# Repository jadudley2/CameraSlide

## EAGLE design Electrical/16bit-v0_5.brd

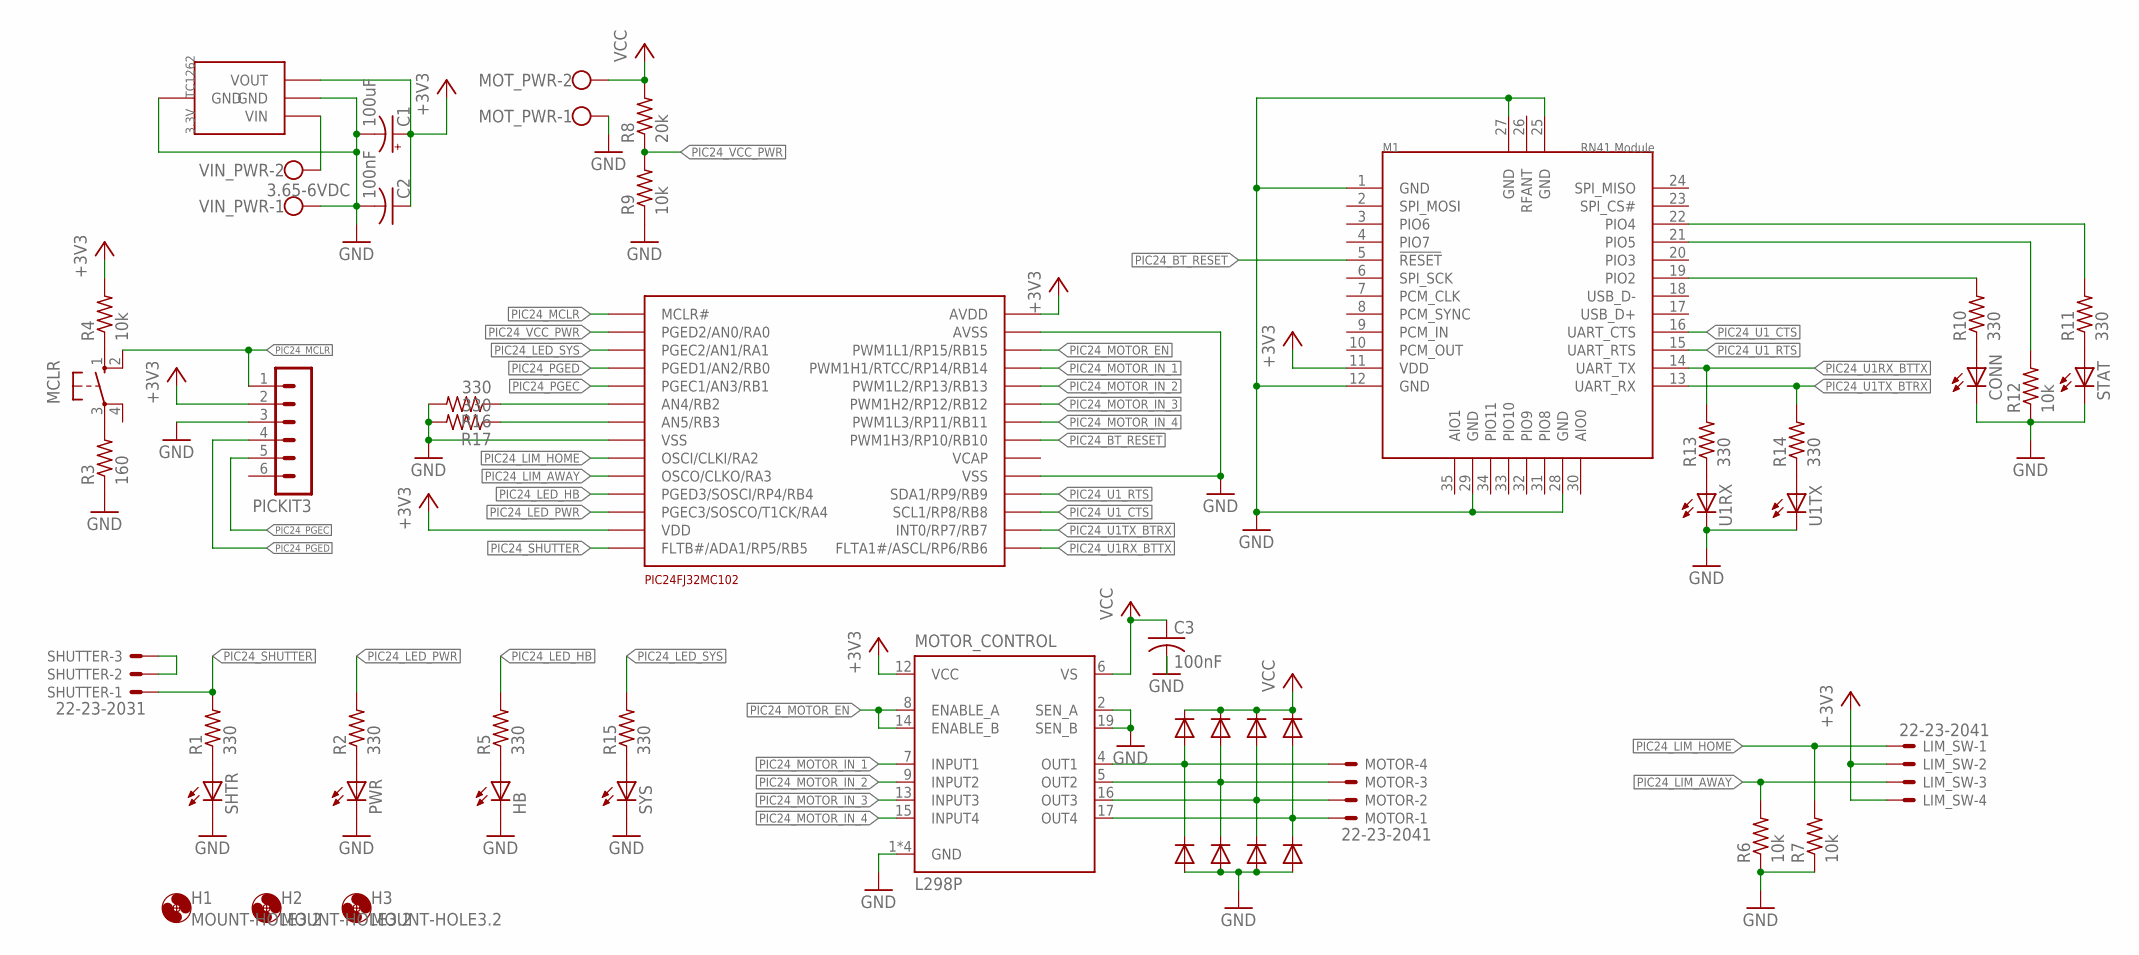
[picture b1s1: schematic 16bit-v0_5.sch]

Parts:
C1: 100uF; E2,5-7
C2, C3: 100nF; C0402
CONN: LED_ESML0603; LED_SML0603
D1, D2, D3, D4, D5, D6, D7, D8: DIODE-SMB; SMB
H1, H2, H3: MOUNT-HOLE3.2; 3,2
HB: LED_ESML0603; LED_SML0603
LIM_SW: 22-23-2041
MCLR: 10-XX; B3F-10XX
MOTOR: 22-23-2041
MOTOR_CONTROL: L298P; POWERSO-20
MOT_PWR: W237-102
PICKIT3: MA06-1
PWR: LED_ESML0603; LED_SML0603
R1, R2, R5, R10, R11, R13, R14, R15, R16, R17: 330; R0603
R3: 160; R0603
R4, R6, R7, R9, R12: 10k; R0603
R8: 20k; R0603
SHTR: LED_ESML0603; LED_SML0603
SHUTTER: 22-23-2031
STAT: LED_ESML0603; LED_SML0603
SYS: LED_ESML0603; LED_SML0603
U1RX, U1TX: LED_ESML0603; LED_SML0603
U$1: PIC24FJ32MC102; PIC2428-SOIC
U$2: RN41N
U$3: TC1262-3.3VDBTR; TO-261-4
VIN_PWR: 3.65-6VDC; W237-102

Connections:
+3V3: C1.+, C2.1, LIM_SW.2, LIM_SW.4, MOTOR_CONTROL.12 (VCC), PICKIT3.2, R4.2, U$1.AVDD, U$1.VDD, U$2.11 (VDD), U$3.P$3 (VOUT)
GND: C1.-, C2.2, C3.2, CONN.C, D5.A, D6.A, D7.A, D8.A, HB.C, MOTOR_CONTROL.1 (GND), MOTOR_CONTROL.2 (SEN_A), MOTOR_CONTROL.10 (GND), MOTOR_CONTROL.11 (GND), MOTOR_CONTROL.19 (SEN_B), MOTOR_CONTROL.20 (GND), MOT_PWR.1, PICKIT3.3, PWR.C, R3.1, R6.1, R7.1, R9.1, R12.1, R16.2, R17.2, SHTR.C, STAT.C, SYS.C, U1RX.C, U1TX.C, U$1.AVSS, U$1.VSS@8 (VSS), U$1.VSS@19 (VSS), U$2.1 (GND), U$2.12 (GND), U$2.25 (GND), U$2.27 (GND), U$2.28 (GND), U$2.29 (GND), U$3.P$2 (GND), U$3.P$4 (GND), VIN_PWR.1
MOTOR_OUT_1: D1.A, D5.C, MOTOR.4, MOTOR_CONTROL.4 (OUT1)
MOTOR_OUT_2: D2.A, D6.C, MOTOR.3, MOTOR_CONTROL.5 (OUT2)
MOTOR_OUT_3: D3.A, D7.C, MOTOR.2, MOTOR_CONTROL.16 (OUT3)
MOTOR_OUT_4: D4.A, D8.C, MOTOR.1, MOTOR_CONTROL.17 (OUT4)
unnamed: R13.1, U1RX.A
unnamed: MCLR.3, R3.2
unnamed: MCLR.1 (S), R4.1
unnamed: R1.1, SHTR.A
unnamed: R12.2, U$2.21 (PIO5)
unnamed: PWR.A, R2.1
unnamed: HB.A, R5.1
unnamed: R15.1, SYS.A
unnamed: R14.1, U1TX.A
unnamed: R11.2, U$2.22 (PIO4)
unnamed: R10.2, U$2.19 (PIO2)
unnamed: CONN.A, R10.1
unnamed: R11.1, STAT.A
PIC24_BT_!RESET: U$1.RB10 (PWM1H3/RP10/RB10), U$2.5 (!RESET)
PIC24_EXTRA_1: R16.1, U$1.RB2 (AN4/RB2)
PIC24_EXTRA_2: R17.1, U$1.RB3 (AN5/RB3)
PIC24_LED_HB: R5.2, U$1.RB4 (PGED3/SOSCI/RP4/RB4)
PIC24_LED_PWR: R2.2, U$1.RA4 (PGEC3/SOSCO/T1CK/RA4)
PIC24_LED_SYS: R15.2, U$1.RA1 (PGEC2/AN1/RA1)
PIC24_LIM_AWAY: LIM_SW.3, R6.2, U$1.RA3 (OSCO/CLKO/RA3)
PIC24_LIM_HOME: LIM_SW.1, R7.2, U$1.RA2 (OSCI/CLKI/RA2)
PIC24_MCLR: MCLR.2 (S1), PICKIT3.1, U$1.MCLR#
PIC24_MOTOR_EN: MOTOR_CONTROL.8 (ENABLE_A), MOTOR_CONTROL.14 (ENABLE_B), U$1.RB15 (PWM1L1/RP15/RB15)
PIC24_MOTOR_IN_1: MOTOR_CONTROL.7 (INPUT1), U$1.RB14 (PWM1H1/RTCC/RP14/RB14)
PIC24_MOTOR_IN_2: MOTOR_CONTROL.9 (INPUT2), U$1.RB13 (PWM1L2/RP13/RB13)
PIC24_MOTOR_IN_3: MOTOR_CONTROL.13 (INPUT3), U$1.RB12 (PWM1H2/RP12/RB12)
PIC24_MOTOR_IN_4: MOTOR_CONTROL.15 (INPUT4), U$1.RB11 (PWM1L3/RP11/RB11)
PIC24_PGEC: PICKIT3.5, U$1.PGEC1 (PGEC1/AN3/RB1)
PIC24_PGED: PICKIT3.4, U$1.PGED1 (PGED1/AN2/RB0)
PIC24_SHUTTER: R1.2, SHUTTER.1, U$1.RB5 (FLTB#/ADA1/RP5/RB5)
PIC24_U1RX_BTTX: R13.2, U$1.RB6 (FLTA1#/ASCL/RP6/RB6), U$2.14 (UART_TX)
PIC24_U1TX_BTRX: R14.2, U$1.RB7 (INT0/RP7/RB7), U$2.13 (UART_RX)
PIC24_U1_CTS: U$1.RB8 (SCL1/RP8/RB8), U$2.16 (UART_CTS)
PIC24_U1_RTS: U$1.RB9 (SDA1/RP9/RB9), U$2.15 (UART_RTS)
PIC24_VCC_PWR: R8.1, R9.2, U$1.RA0 (PGED2/AN0/RA0)
SHUTTER_SHORT: SHUTTER.2, SHUTTER.3
VCC: C3.1, D1.C, D2.C, D3.C, D4.C, MOTOR_CONTROL.6 (VS), MOT_PWR.2, R8.2
VIN_PWR: U$3.P$1 (VIN), VIN_PWR.2

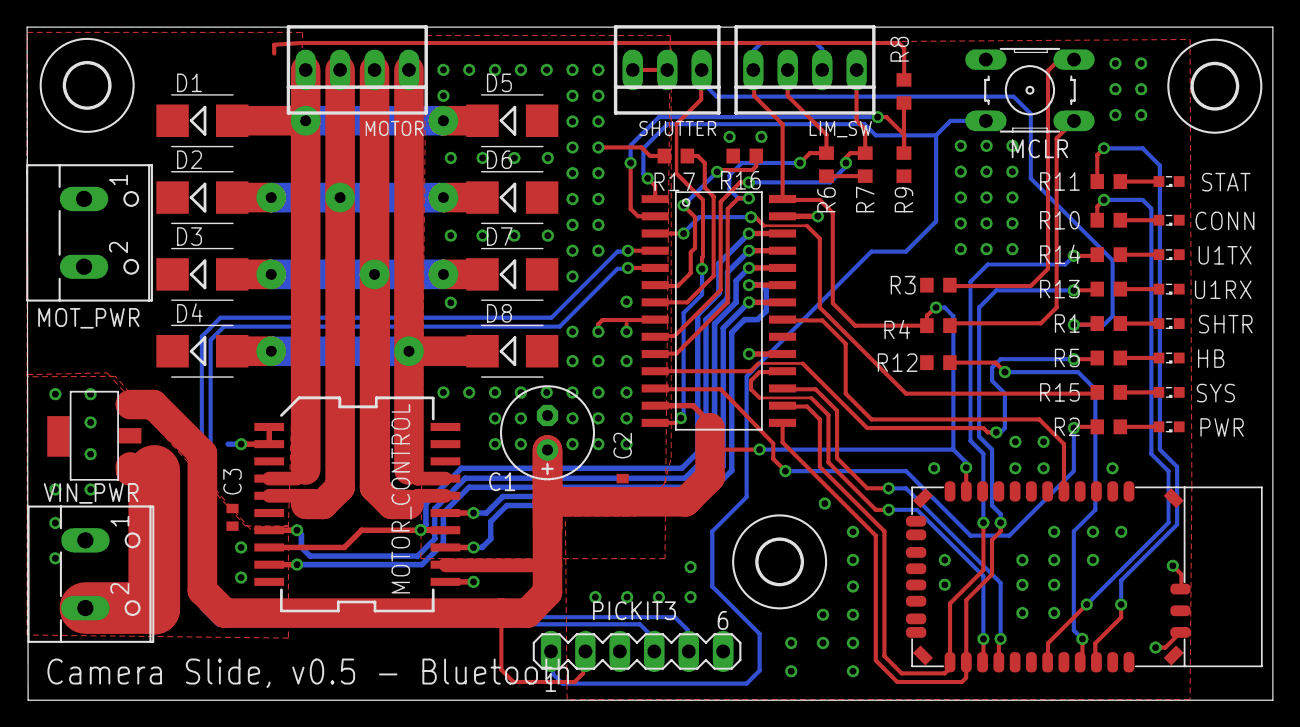
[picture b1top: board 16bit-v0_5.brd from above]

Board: 2 copper layers, 91.9 x 49.7 mm, 50 parts (0 on the bottom side), 44 nets.

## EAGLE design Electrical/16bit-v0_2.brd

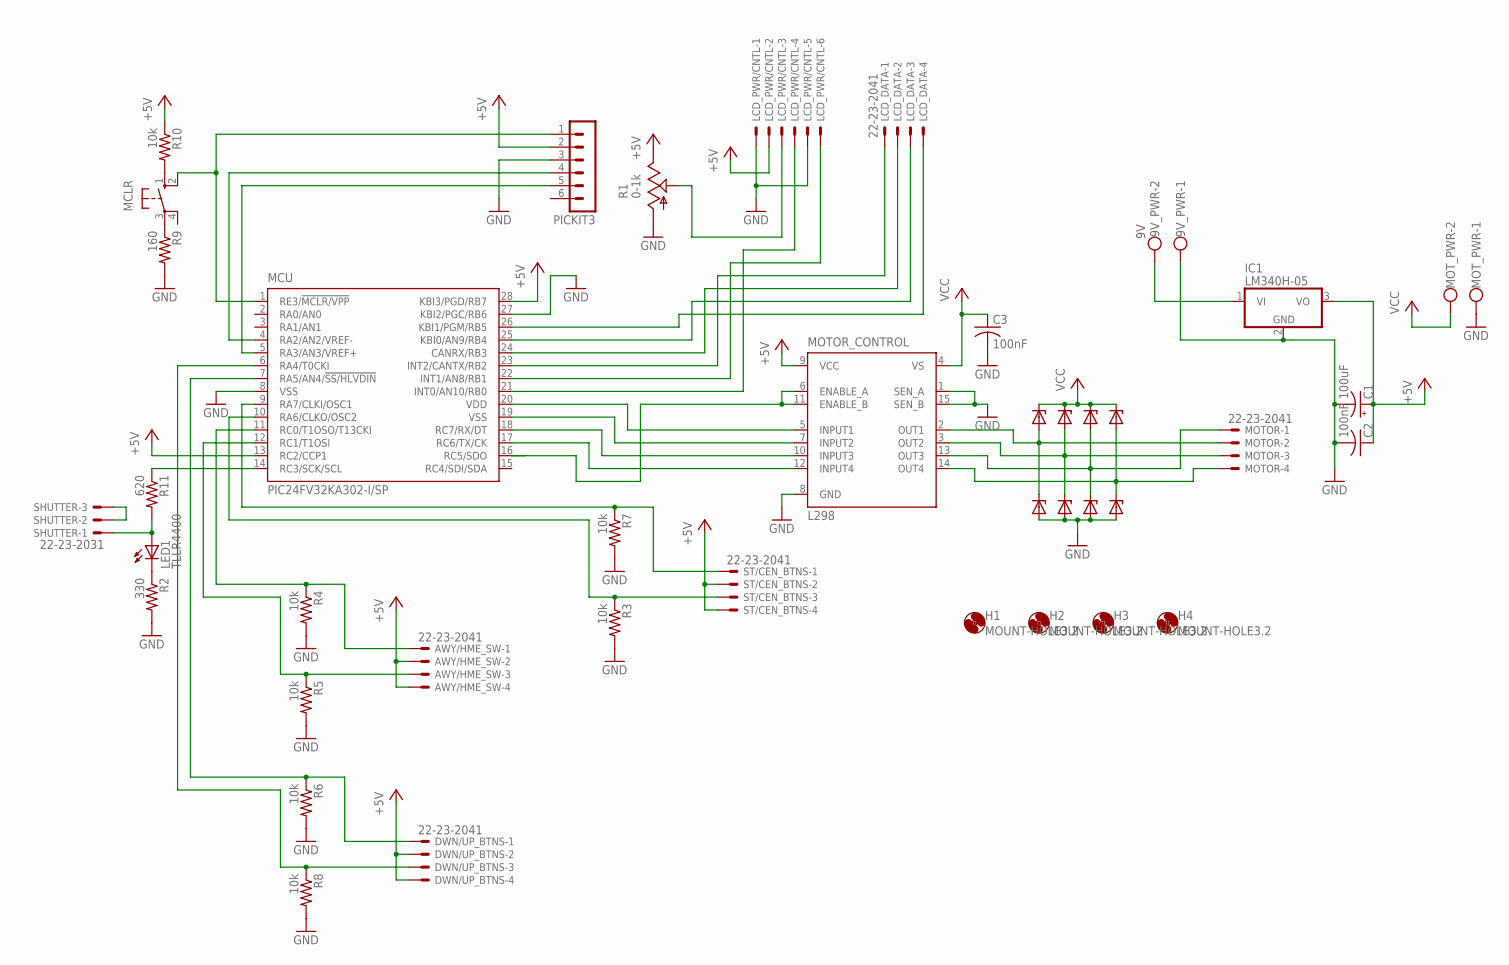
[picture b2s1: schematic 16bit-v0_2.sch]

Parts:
9V_PWR: 9V; W237-102
AWY/HME_SW: 22-23-2041
C1: 100uF; E2,5-7
C2, C3: 100nF; C025-025X050
D1, D2, D3, D4, D5, D6, D7, D8: BZX90; DO34Z7
DWN/UP_BTNS: 22-23-2041
H1, H2, H3, H4: MOUNT-HOLE3.2; 3,2
IC1: LM340H-05; TO220H
LCD_DATA: 22-23-2041
LCD_PWR/CNTL: 22-23-2061
LED1: TLLR4400; LED3MM
MCLR: 10-XX; B3F-10XX
MCU: PIC18F2580-I/SP; DIL28-3; MPN PIC24FV32KA302-I/SP
MOTOR: 22-23-2041
MOTOR_CONTROL: L298; MULTIWATT-15
MOT_PWR: W237-102
PICKIT3: MA06-1
R1: 0-1k; B25P
R2: 330; 0207/7
R3, R4, R5, R6, R7, R8, R10: 10k; 0207/7
R9: 160; 0207/7
R11: 620; 0207/7
SHUTTER: 22-23-2031
ST/CEN_BTNS: 22-23-2041

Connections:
+5V: AWY/HME_SW.2, AWY/HME_SW.4, C1.+, C2.1, DWN/UP_BTNS.2, DWN/UP_BTNS.4, IC1.3 (VO), LCD_PWR/CNTL.2, MCU.13 (RC2/CCP1), MCU.28 (KBI3/PGD/RB7), MOTOR_CONTROL.9 (VCC), PICKIT3.2, R1.E, R10.1, ST/CEN_BTNS.2, ST/CEN_BTNS.4
GND: 9V_PWR.1, C1.-, C2.2, C3.2, D5.A, D6.A, D7.A, D8.A, IC1.2 (GND), LCD_PWR/CNTL.1, LCD_PWR/CNTL.5, MCU.8 (VSS), MCU.27 (KBI2/PGC/RB6), MOTOR_CONTROL.8 (GND), MOT_PWR.1, PICKIT3.3, R1.A, R2.2, R3.2, R4.2, R5.2, R6.2, R7.2, R8.2, R9.2
unnamed: MCLR.2 (S1), MCU.1 (RE3/!MCLR/VPP), PICKIT3.1
unnamed: MCU.5 (RA3/AN3/VREF+), PICKIT3.5
unnamed: MCU.4 (RA2/AN2/VREF-), PICKIT3.4
unnamed: LED1.K (C), R2.1
unnamed: MOTOR_CONTROL.1 (SEN_A), MOTOR_CONTROL.15 (SEN_B)
unnamed: MCU.14 (RC3/SCK/SCL), R11.1
unnamed: MCU.16 (RC5/SDO), MOTOR_CONTROL.6 (ENABLE_A), MOTOR_CONTROL.11 (ENABLE_B)
unnamed: LCD_PWR/CNTL.3, R1.S
unnamed: LCD_PWR/CNTL.4, MCU.21 (INT0/AN10/RB0)
unnamed: LCD_PWR/CNTL.6, MCU.22 (INT1/AN8/RB1)
unnamed: LCD_DATA.2, MCU.24 (CANRX/RB3)
unnamed: LCD_DATA.3, MCU.25 (KBI0/AN9/RB4)
unnamed: LCD_DATA.4, MCU.26 (KBI1/PGM/RB5)
unnamed: MCU.17 (RC6/TX/CK), MOTOR_CONTROL.12 (INPUT4)
unnamed: AWY/HME_SW.1, MCU.11 (RC0/T1OSO/T13CKI), R4.1
unnamed: D2.A, D6.C, MOTOR.3, MOTOR_CONTROL.3 (OUT2)
unnamed: D3.A, D7.C, MOTOR.1, MOTOR_CONTROL.13 (OUT3)
unnamed: D4.A, D8.C, MOTOR.4, MOTOR_CONTROL.14 (OUT4)
unnamed: LED1.A, R11.2, SHUTTER.1
unnamed: LCD_DATA.1, MCU.23 (INT2/CANTX/RB2)
unnamed: MCU.10 (RA6/CLKO/OSC2), R3.1, ST/CEN_BTNS.3
unnamed: MCU.18 (RC7/RX/DT), MOTOR_CONTROL.10 (INPUT3)
unnamed: DWN/UP_BTNS.1, MCU.7 (RA5/AN4/!SS/HLVDIN), R6.1
unnamed: MCU.9 (RA7/CLKI/OSC1), R7.1, ST/CEN_BTNS.1
unnamed: DWN/UP_BTNS.3, MCU.6 (RA4/T0CKI), R8.1
unnamed: MCU.19 (VSS), MOTOR_CONTROL.7 (INPUT2)
unnamed: AWY/HME_SW.3, MCU.12 (RC1/T1OSI), R5.1
unnamed: D1.A, D5.C, MOTOR.2, MOTOR_CONTROL.2 (OUT1)
unnamed: MCU.20 (VDD), MOTOR_CONTROL.5 (INPUT1)
unnamed: MCLR.1 (S), R10.2
unnamed: SHUTTER.2, SHUTTER.3
unnamed: MCLR.3, R9.1
unnamed: 9V_PWR.2, IC1.1 (VI)
VCC: C3.1, D1.C, D2.C, D3.C, D4.C, MOTOR_CONTROL.4 (VS), MOT_PWR.2

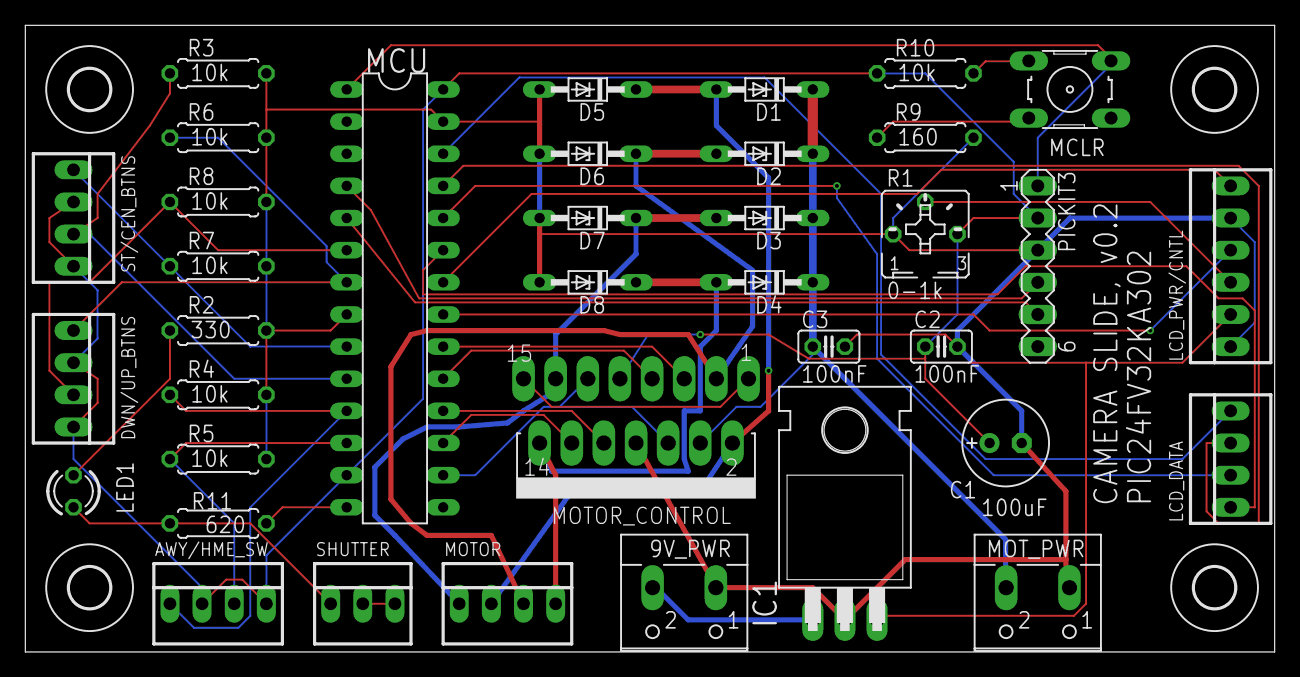
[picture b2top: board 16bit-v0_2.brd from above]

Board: 2 copper layers, 98.7 x 49.5 mm, 41 parts (0 on the bottom side), 36 nets.

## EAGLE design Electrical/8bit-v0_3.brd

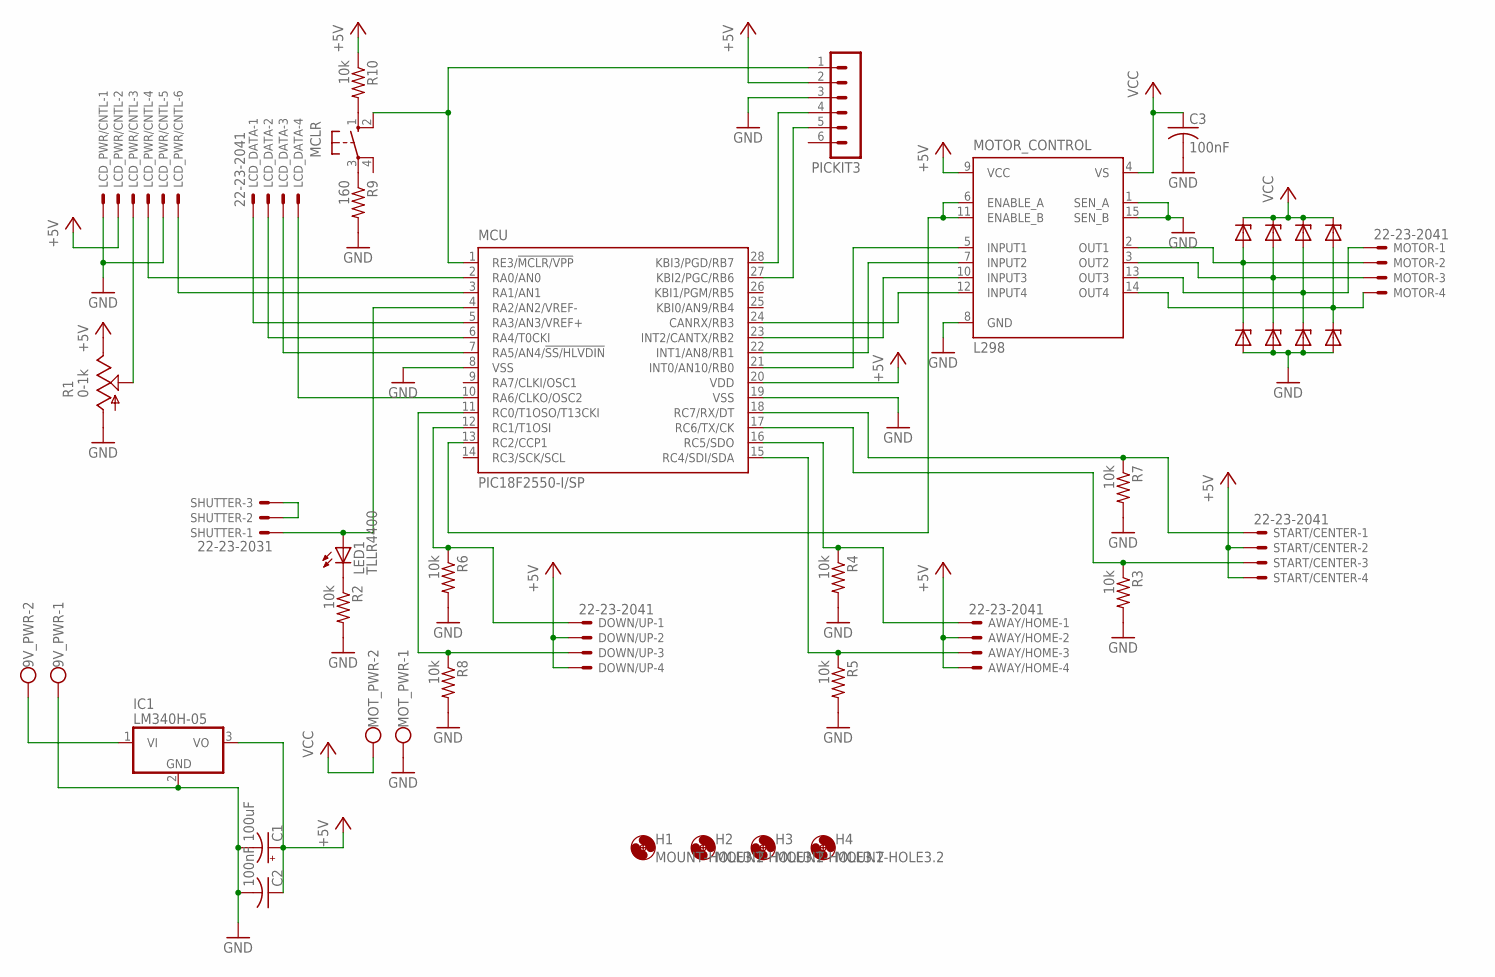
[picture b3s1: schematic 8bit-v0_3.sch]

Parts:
9V_PWR: W237-102
AWAY/HOME: 22-23-2041
C1: 100uF; E2,5-7
C2, C3: 100nF; C025-025X050
D1, D2, D3, D4, D5, D6, D7, D8: BZX90; DO34Z7
DOWN/UP: 22-23-2041
H1, H2, H3, H4: MOUNT-HOLE3.2; 3,2
IC1: LM340H-05; TO220H
LCD_DATA: 22-23-2041
LCD_PWR/CNTL: 22-23-2061
LED1: TLLR4400; LED3MM
MCLR: 10-XX; B3F-10XX
MCU: PIC18F2580-I/SP; DIL28-3; MPN PIC18F2550-I/SP
MOTOR: 22-23-2041
MOTOR_CONTROL: L298; MULTIWATT-15
MOT_PWR: W237-102
PICKIT3: MA06-1
R1: 0-1k; B25P
R2, R3, R4, R5, R6, R7, R8, R10: 10k; 0207/10
R9: 160; 0207/10
SHUTTER: 22-23-2031
START/CENTER: 22-23-2041

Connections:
+5V: AWAY/HOME.2, AWAY/HOME.4, C1.+, C2.1, DOWN/UP.2, DOWN/UP.4, IC1.3 (VO), LCD_PWR/CNTL.2, MCU.20 (VDD), MOTOR_CONTROL.9 (VCC), PICKIT3.2, R1.E, R10.1, START/CENTER.2, START/CENTER.4
GND: 9V_PWR.1, C1.-, C2.2, C3.2, D5.A, D6.A, D7.A, D8.A, IC1.2 (GND), LCD_PWR/CNTL.1, LCD_PWR/CNTL.5, MCU.8 (VSS), MCU.19 (VSS), MOTOR_CONTROL.8 (GND), MOT_PWR.1, PICKIT3.3, R1.A, R2.2, R3.2, R4.2, R5.2, R6.2, R7.2, R8.2, R9.2
unnamed: MCLR.2 (S1), MCU.1 (RE3/!MCLR/VPP), PICKIT3.1
unnamed: MCU.27 (KBI2/PGC/RB6), PICKIT3.5
unnamed: MCU.28 (KBI3/PGD/RB7), PICKIT3.4
unnamed: LCD_PWR/CNTL.3, R1.S
unnamed: MOTOR_CONTROL.1 (SEN_A), MOTOR_CONTROL.15 (SEN_B)
unnamed: MCU.24 (CANRX/RB3), MOTOR_CONTROL.12 (INPUT4)
unnamed: MCU.23 (INT2/CANTX/RB2), MOTOR_CONTROL.10 (INPUT3)
unnamed: MCU.22 (INT1/AN8/RB1), MOTOR_CONTROL.7 (INPUT2)
unnamed: LCD_PWR/CNTL.4, MCU.2 (RA0/AN0)
unnamed: LCD_PWR/CNTL.6, MCU.3 (RA1/AN1)
unnamed: LCD_DATA.1, MCU.5 (RA3/AN3/VREF+)
unnamed: LCD_DATA.3, MCU.7 (RA5/AN4/!SS/HLVDIN)
unnamed: LCD_DATA.4, MCU.10 (RA6/CLKO/OSC2)
unnamed: MCU.21 (INT0/AN10/RB0), MOTOR_CONTROL.5 (INPUT1)
unnamed: AWAY/HOME.1, MCU.16 (RC5/SDO), R4.1
unnamed: D2.A, D6.C, MOTOR.3, MOTOR_CONTROL.3 (OUT2)
unnamed: D3.A, D7.C, MOTOR.1, MOTOR_CONTROL.13 (OUT3)
unnamed: D4.A, D8.C, MOTOR.4, MOTOR_CONTROL.14 (OUT4)
unnamed: AWAY/HOME.3, MCU.15 (RC4/SDI/SDA), R5.1
unnamed: LCD_DATA.2, MCU.6 (RA4/T0CKI)
unnamed: MCU.17 (RC6/TX/CK), R3.1, START/CENTER.3
unnamed: LED1.K (C), R2.1
unnamed: DOWN/UP.1, MCU.12 (RC1/T1OSI), R6.1
unnamed: MCU.18 (RC7/RX/DT), R7.1, START/CENTER.1
unnamed: DOWN/UP.3, MCU.11 (RC0/T1OSO/T13CKI), R8.1
unnamed: D1.A, D5.C, MOTOR.2, MOTOR_CONTROL.2 (OUT1)
unnamed: MCU.13 (RC2/CCP1), MOTOR_CONTROL.6 (ENABLE_A), MOTOR_CONTROL.11 (ENABLE_B)
unnamed: LED1.A, MCU.4 (RA2/AN2/VREF-), SHUTTER.1
unnamed: MCLR.1 (S), R10.2
unnamed: SHUTTER.2, SHUTTER.3
unnamed: MCLR.3, R9.1
unnamed: 9V_PWR.2, IC1.1 (VI)
VCC: C3.1, D1.C, D2.C, D3.C, D4.C, MOTOR_CONTROL.4 (VS), MOT_PWR.2

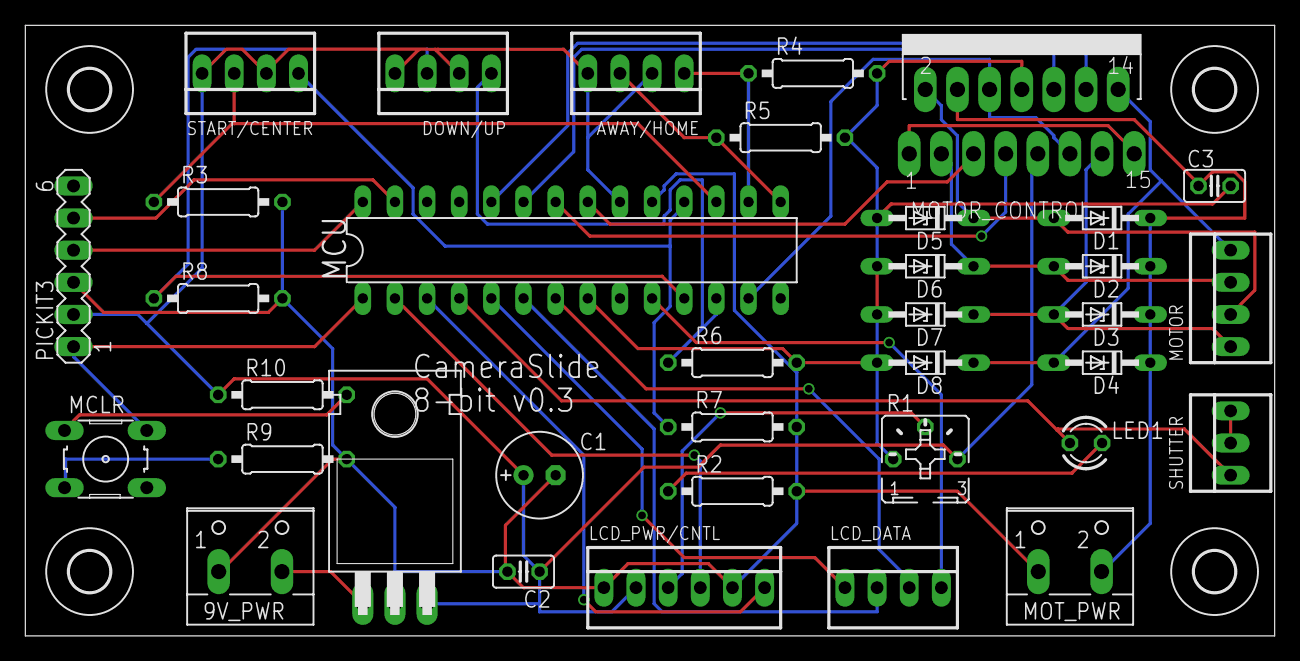
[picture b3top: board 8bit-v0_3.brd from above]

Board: 2 copper layers, 98.7 x 48.2 mm, 40 parts (0 on the bottom side), 35 nets.

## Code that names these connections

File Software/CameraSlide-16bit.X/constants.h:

/* 
 * File:   constants.h
 * Author: James Dudley
 *
 * Created on May 23, 2015, 11:13 AM
 */

#ifndef CONSTANTS_H
#define	CONSTANTS_H

#include <stdio.h>
#include <stdlib.h>
#include <xc.h>

/* general */
#define ON                  1
#define OFF                 0
#define HI                  1
#define LO                  0
#define HOME                6           // home switch
#define AWAY                7           // away switch

/* digital pins */
#define START_BUTTON_PIN    PORTAbits.RA2
#define CENTER_BUTTON_PIN   PORTAbits.RA3
#define UP_BUTTON_PIN       PORTBbits.RB2
#define DOWN_BUTTON_PIN     PORTBbits.RB3

#define HOME_SWITCH_PIN     PORTAbits.RA4
#define AWAY_SWITCH_PIN     PORTBbits.RB4

#define LCD_EN_PIN          LATBbits.LATB10
#define LCD_RS_PIN          LATBbits.LATB11
#define LCD_D4_PIN          LATBbits.LATB12
#define LCD_D5_PIN          LATBbits.LATB13
#define LCD_D6_PIN          LATBbits.LATB14
#define LCD_D7_PIN          LATBbits.LATB15

#define MOTOR_1_PIN         LATBbits.LATB6
#define MOTOR_2_PIN         LATAbits.LATA7
#define MOTOR_3_PIN         LATBbits.LATB9
#define MOTOR_4_PIN         LATBbits.LATB8
#define MOTOR_EN_PIN        LATBbits.LATB7

#define SHUTTER_PIN         LATBbits.LATB5

/* hardware */
#define HOME_POS            0
#define AWAY_POS            6250

/* camera */
#define NUM_SHUTTER_SPEEDS      55

/* LCD */
#define LCD_WIDTH               16
#define SHUTTER_STR_LENGTH      6
#define DIR_STR_LENGTH          4

#endif	/* CONSTANTS_H */

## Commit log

2015-08-13 Adding bluetooth project
2015-12-26 Cleaned up old versions, working on v0.5 bluetooth
2015-12-26 Switched over to interrupt-based UART tx/rx handling
2016-01-09 Added PWR LED with ADC functionality
2016-04-17 Updating to Windows 10
